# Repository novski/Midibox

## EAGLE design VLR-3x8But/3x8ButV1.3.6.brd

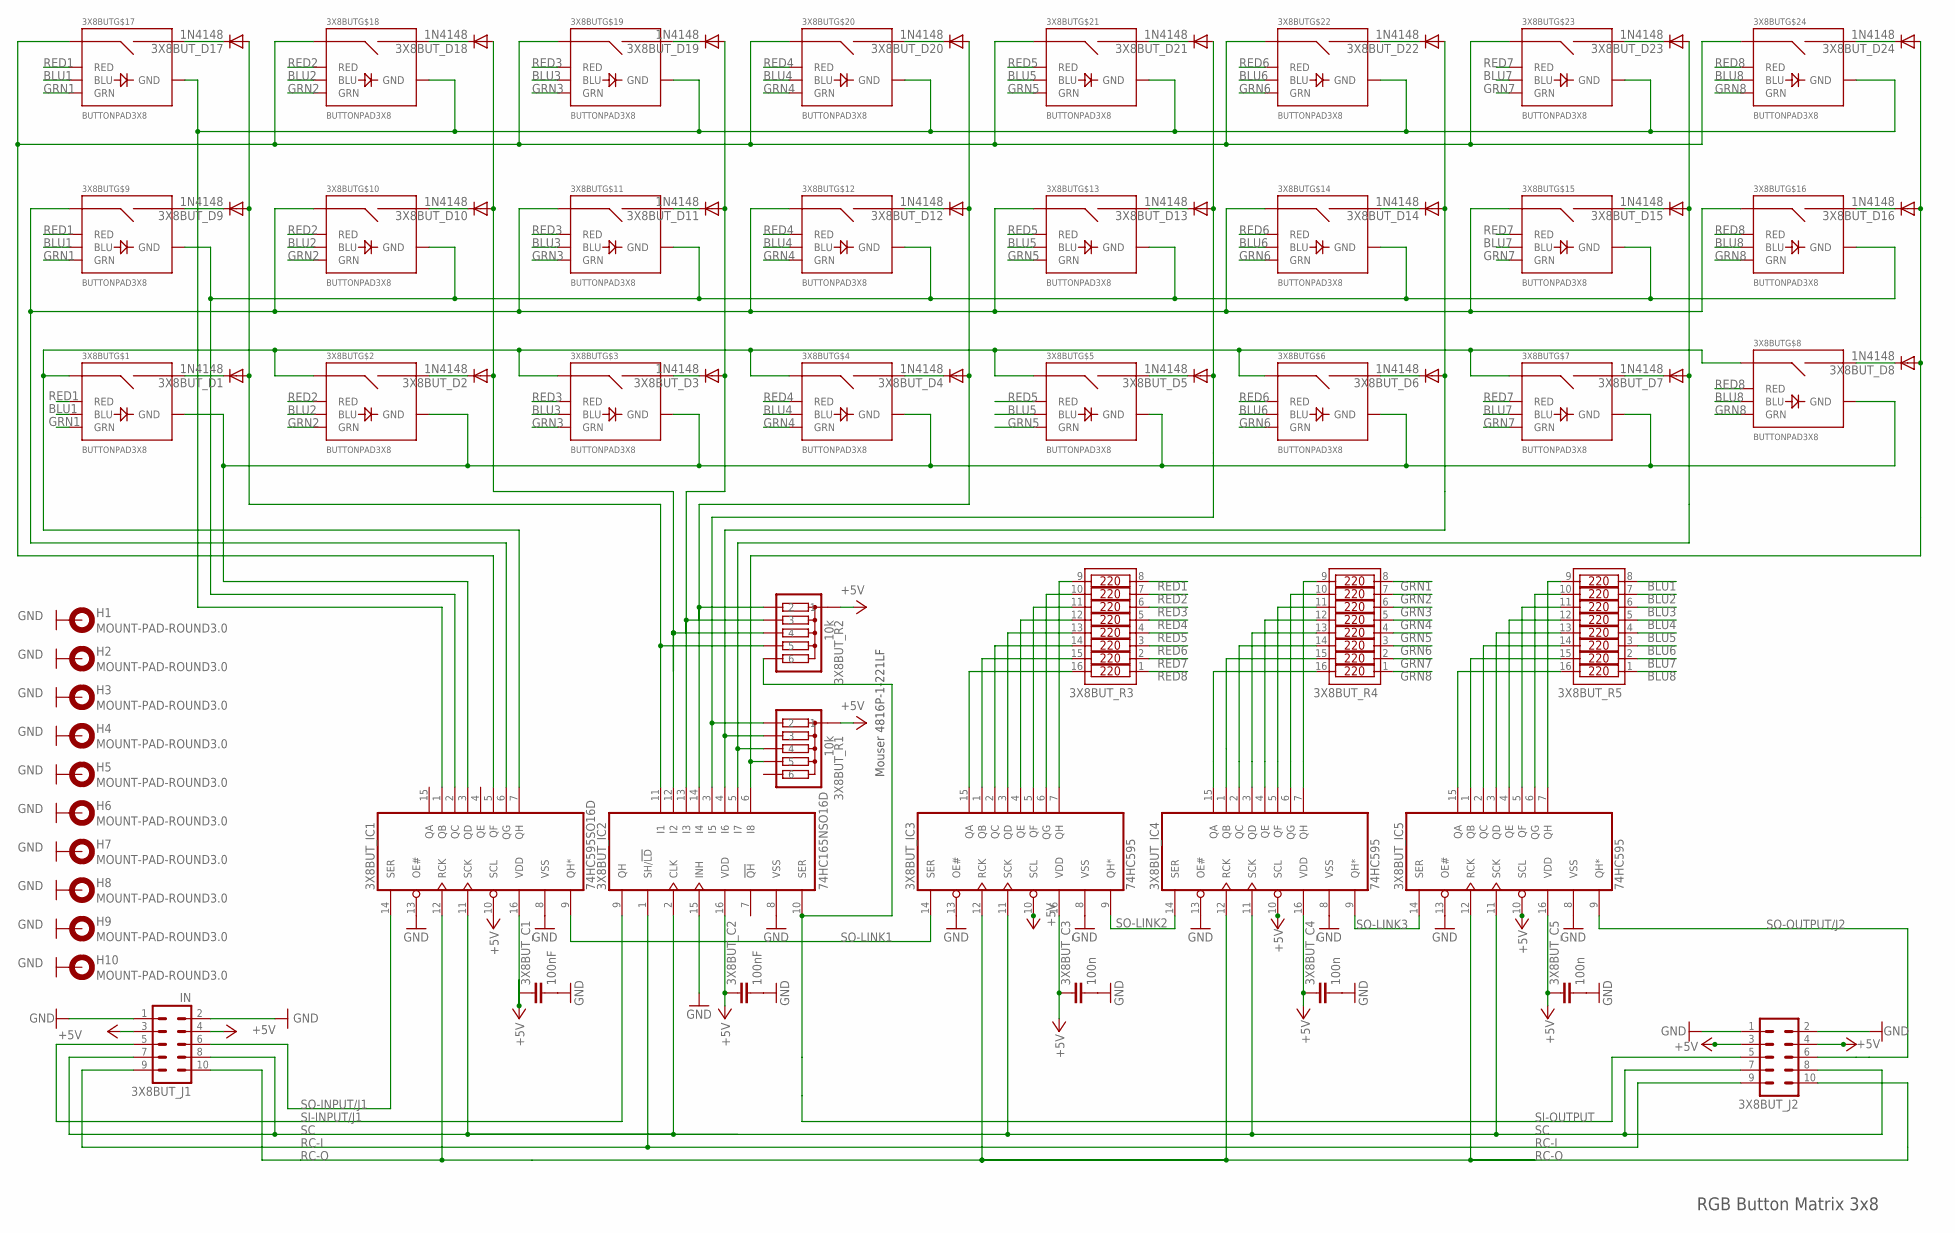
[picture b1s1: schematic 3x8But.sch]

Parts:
3X8BUT: BUTTONPAD3X8
3X8BUT_C1, 3X8BUT_C2: 100nF; C025-030X050
3X8BUT_C3, 3X8BUT_C4, 3X8BUT_C5: 100n; C025-030X050
3X8BUT_D1, 3X8BUT_D2, 3X8BUT_D3, 3X8BUT_D4, 3X8BUT_D5, 3X8BUT_D6, 3X8BUT_D7, 3X8BUT_D8, 3X8BUT_D9, 3X8BUT_D10, 3X8BUT_D11, 3X8BUT_D12, 3X8BUT_D13, 3X8BUT_D14, 3X8BUT_D15, 3X8BUT_D16, 3X8BUT_D17, 3X8BUT_D18, 3X8BUT_D19, 3X8BUT_D20, 3X8BUT_D21, 3X8BUT_D22, 3X8BUT_D23, 3X8BUT_D24: 1N4148; DO35-7
3X8BUT_IC1: 74HC595SO16D; SO16D
3X8BUT_IC2: 74HC165NSO16D; SO16D
3X8BUT_IC3, 3X8BUT_IC4, 3X8BUT_IC5: 74HC595; SO16D
3X8BUT_J1: IN; ML10
3X8BUT_J2: ML10
3X8BUT_R1, 3X8BUT_R2: 10k; SIL6
3X8BUT_R3, 3X8BUT_R4, 3X8BUT_R5: 4816P-1SOIC16W; SOIC16W
H1, H2, H3, H4, H5, H6, H7, H8, H9, H10: MOUNT-PAD-ROUND3.0; 3,0-PAD

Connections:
+5V: 3X8BUT_C1.1, 3X8BUT_C2.1, 3X8BUT_C3.1, 3X8BUT_C4.1, 3X8BUT_C5.1, 3X8BUT_IC1.10 (SCL), 3X8BUT_IC1.16 (VDD), 3X8BUT_IC2.16 (VDD), 3X8BUT_IC3.10 (SCL), 3X8BUT_IC3.16 (VDD), 3X8BUT_IC4.10 (SCL), 3X8BUT_IC4.16 (VDD), 3X8BUT_IC5.10 (SCL), 3X8BUT_IC5.16 (VDD), 3X8BUT_J1.3, 3X8BUT_J1.4, 3X8BUT_J2.3, 3X8BUT_J2.4, 3X8BUT_R1.1, 3X8BUT_R2.1
BLU1: 3X8BUT.BLU1 (BLU), 3X8BUT.BLU9 (BLU), 3X8BUT.BLU17 (BLU), 3X8BUT_R5.8
BLU2: 3X8BUT.BLU2 (BLU), 3X8BUT.BLU10 (BLU), 3X8BUT.BLU18 (BLU), 3X8BUT_R5.7
BLU3: 3X8BUT.BLU3 (BLU), 3X8BUT.BLU11 (BLU), 3X8BUT.BLU19 (BLU), 3X8BUT_R5.6
BLU4: 3X8BUT.BLU4 (BLU), 3X8BUT.BLU12 (BLU), 3X8BUT.BLU20 (BLU), 3X8BUT_R5.5
BLU5: 3X8BUT.BLU5 (BLU), 3X8BUT.BLU13 (BLU), 3X8BUT.BLU21 (BLU), 3X8BUT_R5.4
BLU6: 3X8BUT.BLU6 (BLU), 3X8BUT.BLU14 (BLU), 3X8BUT.BLU22 (BLU), 3X8BUT_R5.3
BLU7: 3X8BUT.BLU7 (BLU), 3X8BUT.BLU15 (BLU), 3X8BUT.BLU23 (BLU), 3X8BUT_R5.2
BLU8: 3X8BUT.BLU8 (BLU), 3X8BUT.BLU16 (BLU), 3X8BUT.BLU24 (BLU), 3X8BUT_R5.1
GND: 3X8BUT_C1.2, 3X8BUT_C2.2, 3X8BUT_C3.2, 3X8BUT_C4.2, 3X8BUT_C5.2, 3X8BUT_IC1.8 (VSS), 3X8BUT_IC1.13 (OE#), 3X8BUT_IC2.8 (VSS), 3X8BUT_IC2.15 (INH), 3X8BUT_IC3.8 (VSS), 3X8BUT_IC3.13 (OE#), 3X8BUT_IC4.8 (VSS), 3X8BUT_IC4.13 (OE#), 3X8BUT_IC5.8 (VSS), 3X8BUT_IC5.13 (OE#), 3X8BUT_J1.1, 3X8BUT_J1.2, 3X8BUT_J2.1, 3X8BUT_J2.2, H1.B3,0, H2.B3,0, H3.B3,0, H4.B3,0, H5.B3,0, H6.B3,0, H7.B3,0, H8.B3,0, H9.B3,0, H10.B3,0
GND1: 3X8BUT.GND1 (GND), 3X8BUT.GND2 (GND), 3X8BUT.GND3 (GND), 3X8BUT.GND4 (GND), 3X8BUT.GND5 (GND), 3X8BUT.GND6 (GND), 3X8BUT.GND7 (GND), 3X8BUT.GND8 (GND), 3X8BUT_IC1.3 (QD)
GND9: 3X8BUT.GND9 (GND), 3X8BUT.GND10 (GND), 3X8BUT.GND11 (GND), 3X8BUT.GND12 (GND), 3X8BUT.GND13 (GND), 3X8BUT.GND14 (GND), 3X8BUT.GND15 (GND), 3X8BUT.GND16 (GND), 3X8BUT_IC1.2 (QC)
GND17: 3X8BUT.GND17 (GND), 3X8BUT.GND18 (GND), 3X8BUT.GND19 (GND), 3X8BUT.GND20 (GND), 3X8BUT.GND21 (GND), 3X8BUT.GND22 (GND), 3X8BUT.GND23 (GND), 3X8BUT.GND24 (GND), 3X8BUT_IC1.1 (QB)
GRN1: 3X8BUT.GRN1 (GRN), 3X8BUT.GRN9 (GRN), 3X8BUT.GRN17 (GRN), 3X8BUT_R4.8
GRN2: 3X8BUT.GRN2 (GRN), 3X8BUT.GRN10 (GRN), 3X8BUT.GRN18 (GRN), 3X8BUT_R4.7
GRN3: 3X8BUT.GRN3 (GRN), 3X8BUT.GRN11 (GRN), 3X8BUT.GRN19 (GRN), 3X8BUT_R4.6
GRN4: 3X8BUT.GRN4 (GRN), 3X8BUT.GRN12 (GRN), 3X8BUT.GRN20 (GRN), 3X8BUT_R4.5
GRN5: 3X8BUT.GRN5 (GRN), 3X8BUT.GRN13 (GRN), 3X8BUT.GRN21 (GRN), 3X8BUT_R4.4
GRN6: 3X8BUT.GRN6 (GRN), 3X8BUT.GRN14 (GRN), 3X8BUT.GRN22 (GRN), 3X8BUT_R4.3
GRN7: 3X8BUT.GRN7 (GRN), 3X8BUT.GRN15 (GRN), 3X8BUT.GRN23 (GRN), 3X8BUT_R4.2
GRN8: 3X8BUT.GRN8 (GRN), 3X8BUT.GRN16 (GRN), 3X8BUT.GRN24 (GRN), 3X8BUT_R4.1
unnamed: 3X8BUT.SIG34 (SIG2), 3X8BUT_D17.C
unnamed: 3X8BUT.SIG18 (SIG2), 3X8BUT_D9.C
unnamed: 3X8BUT.SIG02 (SIG2), 3X8BUT_D1.C
unnamed: 3X8BUT.SIG36 (SIG2), 3X8BUT_D18.C
unnamed: 3X8BUT.SIG20 (SIG2), 3X8BUT_D10.C
unnamed: 3X8BUT.SIG04 (SIG2), 3X8BUT_D2.C
unnamed: 3X8BUT.SIG38 (SIG2), 3X8BUT_D19.C
unnamed: 3X8BUT.SIG22 (SIG2), 3X8BUT_D11.C
unnamed: 3X8BUT_IC5.15 (QA), 3X8BUT_R5.16
unnamed: 3X8BUT_IC5.1 (QB), 3X8BUT_R5.15
unnamed: 3X8BUT_IC5.2 (QC), 3X8BUT_R5.14
unnamed: 3X8BUT_IC5.3 (QD), 3X8BUT_R5.13
unnamed: 3X8BUT_IC5.4 (QE), 3X8BUT_R5.12
unnamed: 3X8BUT_IC5.5 (QF), 3X8BUT_R5.11
unnamed: 3X8BUT_IC5.6 (QG), 3X8BUT_R5.10
unnamed: 3X8BUT_IC5.7 (QH), 3X8BUT_R5.9
unnamed: 3X8BUT_IC3.15 (QA), 3X8BUT_R3.16
unnamed: 3X8BUT_IC3.1 (QB), 3X8BUT_R3.15
unnamed: 3X8BUT_IC3.2 (QC), 3X8BUT_R3.14
unnamed: 3X8BUT_IC3.3 (QD), 3X8BUT_R3.13
unnamed: 3X8BUT_IC3.4 (QE), 3X8BUT_R3.12
unnamed: 3X8BUT_IC3.5 (QF), 3X8BUT_R3.11
unnamed: 3X8BUT_IC3.6 (QG), 3X8BUT_R3.10
unnamed: 3X8BUT_IC3.7 (QH), 3X8BUT_R3.9
unnamed: 3X8BUT_IC4.15 (QA), 3X8BUT_R4.16
unnamed: 3X8BUT_IC4.1 (QB), 3X8BUT_R4.15
unnamed: 3X8BUT_IC4.2 (QC), 3X8BUT_R4.14
unnamed: 3X8BUT_IC4.3 (QD), 3X8BUT_R4.13
unnamed: 3X8BUT_IC4.4 (QE), 3X8BUT_R4.12
unnamed: 3X8BUT_IC4.5 (QF), 3X8BUT_R4.11
unnamed: 3X8BUT_IC4.6 (QG), 3X8BUT_R4.10
unnamed: 3X8BUT_IC4.7 (QH), 3X8BUT_R4.9
unnamed: 3X8BUT.SIG06 (SIG2), 3X8BUT_D3.C
unnamed: 3X8BUT.SIG40 (SIG2), 3X8BUT_D20.C
unnamed: 3X8BUT.SIG24 (SIG2), 3X8BUT_D12.C
unnamed: 3X8BUT.SIG08 (SIG2), 3X8BUT_D4.C
unnamed: 3X8BUT.SIG42 (SIG2), 3X8BUT_D21.C
unnamed: 3X8BUT.SIG26 (SIG2), 3X8BUT_D13.C
unnamed: 3X8BUT.SIG10 (SIG2), 3X8BUT_D5.C
unnamed: 3X8BUT.SIG44 (SIG2), 3X8BUT_D22.C
unnamed: 3X8BUT.SIG28 (SIG2), 3X8BUT_D14.C
unnamed: 3X8BUT.SIG12 (SIG2), 3X8BUT_D6.C
unnamed: 3X8BUT.SIG14 (SIG2), 3X8BUT_D7.C
unnamed: 3X8BUT.SIG30 (SIG2), 3X8BUT_D15.C
unnamed: 3X8BUT.SIG46 (SIG2), 3X8BUT_D23.C
unnamed: 3X8BUT.SIG48 (SIG2), 3X8BUT_D24.C
unnamed: 3X8BUT.SIG32 (SIG2), 3X8BUT_D16.C
unnamed: 3X8BUT.SIG16 (SIG2), 3X8BUT_D8.C
RC-I: 3X8BUT_IC2.1 (SH/!LD), 3X8BUT_J1.9, 3X8BUT_J2.9
RC-O: 3X8BUT_IC1.12 (RCK), 3X8BUT_IC3.12 (RCK), 3X8BUT_IC4.12 (RCK), 3X8BUT_IC5.12 (RCK), 3X8BUT_J1.10, 3X8BUT_J2.10
RED1: 3X8BUT.RED1 (RED), 3X8BUT.RED9 (RED), 3X8BUT.RED17 (RED), 3X8BUT_R3.8
RED2: 3X8BUT.RED2 (RED), 3X8BUT.RED10 (RED), 3X8BUT.RED18 (RED), 3X8BUT_R3.7
RED3: 3X8BUT.RED3 (RED), 3X8BUT.RED11 (RED), 3X8BUT.RED19 (RED), 3X8BUT_R3.6
RED4: 3X8BUT.RED4 (RED), 3X8BUT.RED12 (RED), 3X8BUT.RED20 (RED), 3X8BUT_R3.5
RED5: 3X8BUT.RED5 (RED), 3X8BUT.RED13 (RED), 3X8BUT.RED21 (RED), 3X8BUT_R3.4
RED6: 3X8BUT.RED6 (RED), 3X8BUT.RED14 (RED), 3X8BUT.RED22 (RED), 3X8BUT_R3.3
RED7: 3X8BUT.RED7 (RED), 3X8BUT.RED15 (RED), 3X8BUT.RED23 (RED), 3X8BUT_R3.2
RED8: 3X8BUT.RED8 (RED), 3X8BUT.RED16 (RED), 3X8BUT.RED24 (RED), 3X8BUT_R3.1
ROW1: 3X8BUT_D1.A, 3X8BUT_D9.A, 3X8BUT_D17.A, 3X8BUT_IC2.11 (I1), 3X8BUT_R2.5
ROW2: 3X8BUT_D2.A, 3X8BUT_D10.A, 3X8BUT_D18.A, 3X8BUT_IC2.12 (I2), 3X8BUT_R2.4
ROW3: 3X8BUT_D3.A, 3X8BUT_D11.A, 3X8BUT_D19.A, 3X8BUT_IC2.13 (I3), 3X8BUT_R2.3
ROW4: 3X8BUT_D4.A, 3X8BUT_D12.A, 3X8BUT_D20.A, 3X8BUT_IC2.14 (I4), 3X8BUT_R2.2
ROW5: 3X8BUT_D5.A, 3X8BUT_D13.A, 3X8BUT_D21.A, 3X8BUT_IC2.3 (I5), 3X8BUT_R1.2
ROW6: 3X8BUT_D6.A, 3X8BUT_D14.A, 3X8BUT_D22.A, 3X8BUT_IC2.4 (I6), 3X8BUT_R1.3
ROW7: 3X8BUT_D7.A, 3X8BUT_D15.A, 3X8BUT_D23.A, 3X8BUT_IC2.5 (I7), 3X8BUT_R1.4
ROW8: 3X8BUT_D8.A, 3X8BUT_D16.A, 3X8BUT_D24.A, 3X8BUT_IC2.6 (I8), 3X8BUT_R1.5
SC: 3X8BUT_IC1.11 (SCK), 3X8BUT_IC2.2 (CLK), 3X8BUT_IC3.11 (SCK), 3X8BUT_IC4.11 (SCK), 3X8BUT_IC5.11 (SCK), 3X8BUT_J1.7, 3X8BUT_J1.8, 3X8BUT_J2.7, 3X8BUT_J2.8
SEL1: 3X8BUT.SIG01 (SIG1), 3X8BUT.SIG03 (SIG1), 3X8BUT.SIG05 (SIG1), 3X8BUT.SIG07 (SIG1), 3X8BUT.SIG09 (SIG1), 3X8BUT.SIG11 (SIG1), 3X8BUT.SIG13 (SIG1), 3X8BUT.SIG15 (SIG1), 3X8BUT_IC1.7 (QH)
SEL2: 3X8BUT.SIG17 (SIG1), 3X8BUT.SIG19 (SIG1), 3X8BUT.SIG21 (SIG1), 3X8BUT.SIG23 (SIG1), 3X8BUT.SIG25 (SIG1), 3X8BUT.SIG27 (SIG1), 3X8BUT.SIG29 (SIG1), 3X8BUT.SIG31 (SIG1), 3X8BUT_IC1.6 (QG)
SEL3: 3X8BUT.SIG33 (SIG1), 3X8BUT.SIG35 (SIG1), 3X8BUT.SIG37 (SIG1), 3X8BUT.SIG39 (SIG1), 3X8BUT.SIG41 (SIG1), 3X8BUT.SIG43 (SIG1), 3X8BUT.SIG45 (SIG1), 3X8BUT.SIG47 (SIG1), 3X8BUT_IC1.5 (QF)
SI-INPUT/J1: 3X8BUT_IC2.9 (QH), 3X8BUT_J1.5
SI-OUTPUT: 3X8BUT_IC2.10 (SER), 3X8BUT_J2.5, 3X8BUT_R2.6
SO-INPUT/J1: 3X8BUT_IC1.14 (SER), 3X8BUT_J1.6
SO-LINK1: 3X8BUT_IC1.9 (QH*), 3X8BUT_IC3.14 (SER)
SO-LINK2: 3X8BUT_IC3.9 (QH*), 3X8BUT_IC4.14 (SER)
SO-LINK3: 3X8BUT_IC4.9 (QH*), 3X8BUT_IC5.14 (SER)
SO-OUTPUT/J2: 3X8BUT_IC5.9 (QH*), 3X8BUT_J2.6

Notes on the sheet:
RGB Button Matrix 3x8
Mouser 4816P-1-221LF

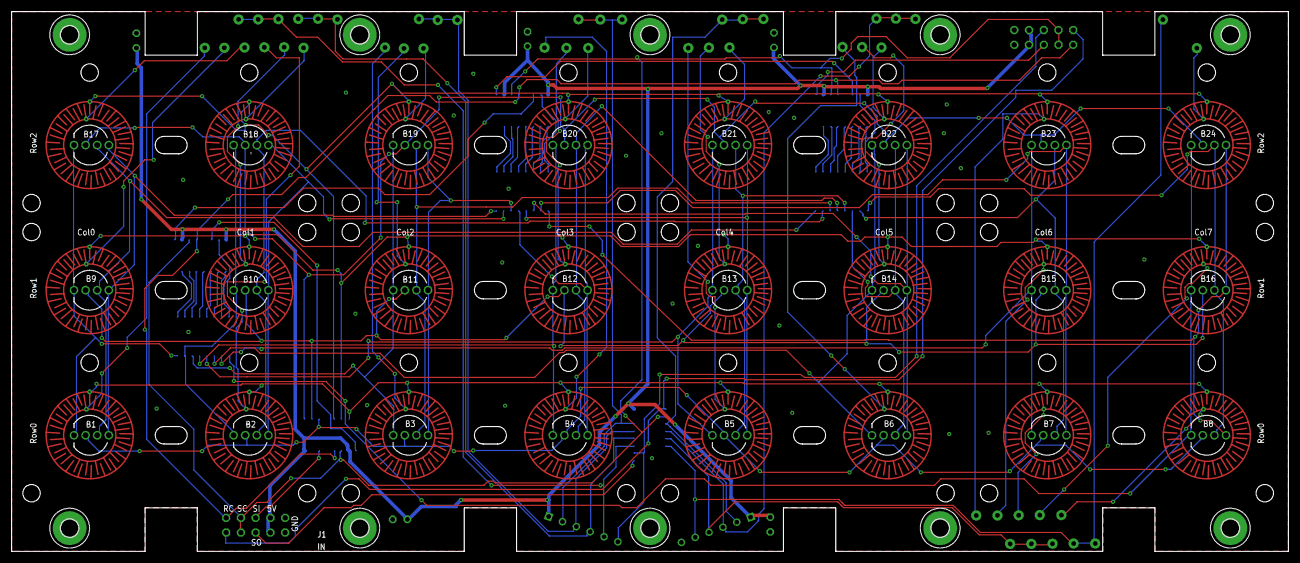
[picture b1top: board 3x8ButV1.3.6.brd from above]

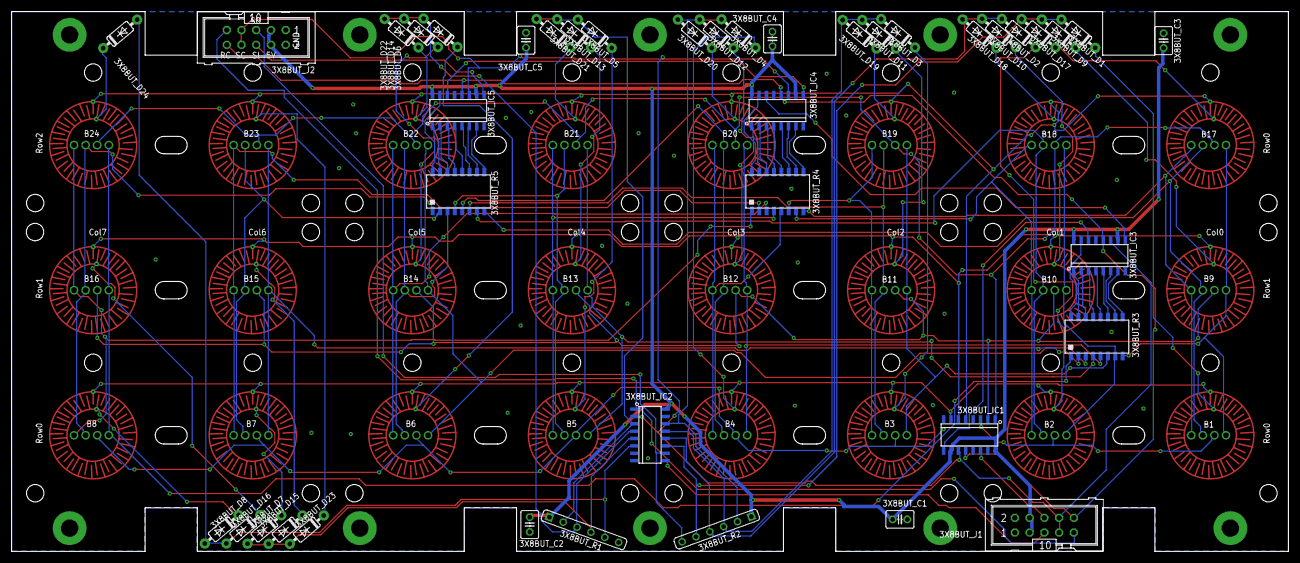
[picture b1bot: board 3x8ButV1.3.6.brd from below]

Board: 2 copper layers, 220.0 x 93.0 mm, 56 parts (43 on the bottom side), 98 nets.

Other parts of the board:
U$1, U$5: VLRLAB
U$3, U$4: 3X8BUT

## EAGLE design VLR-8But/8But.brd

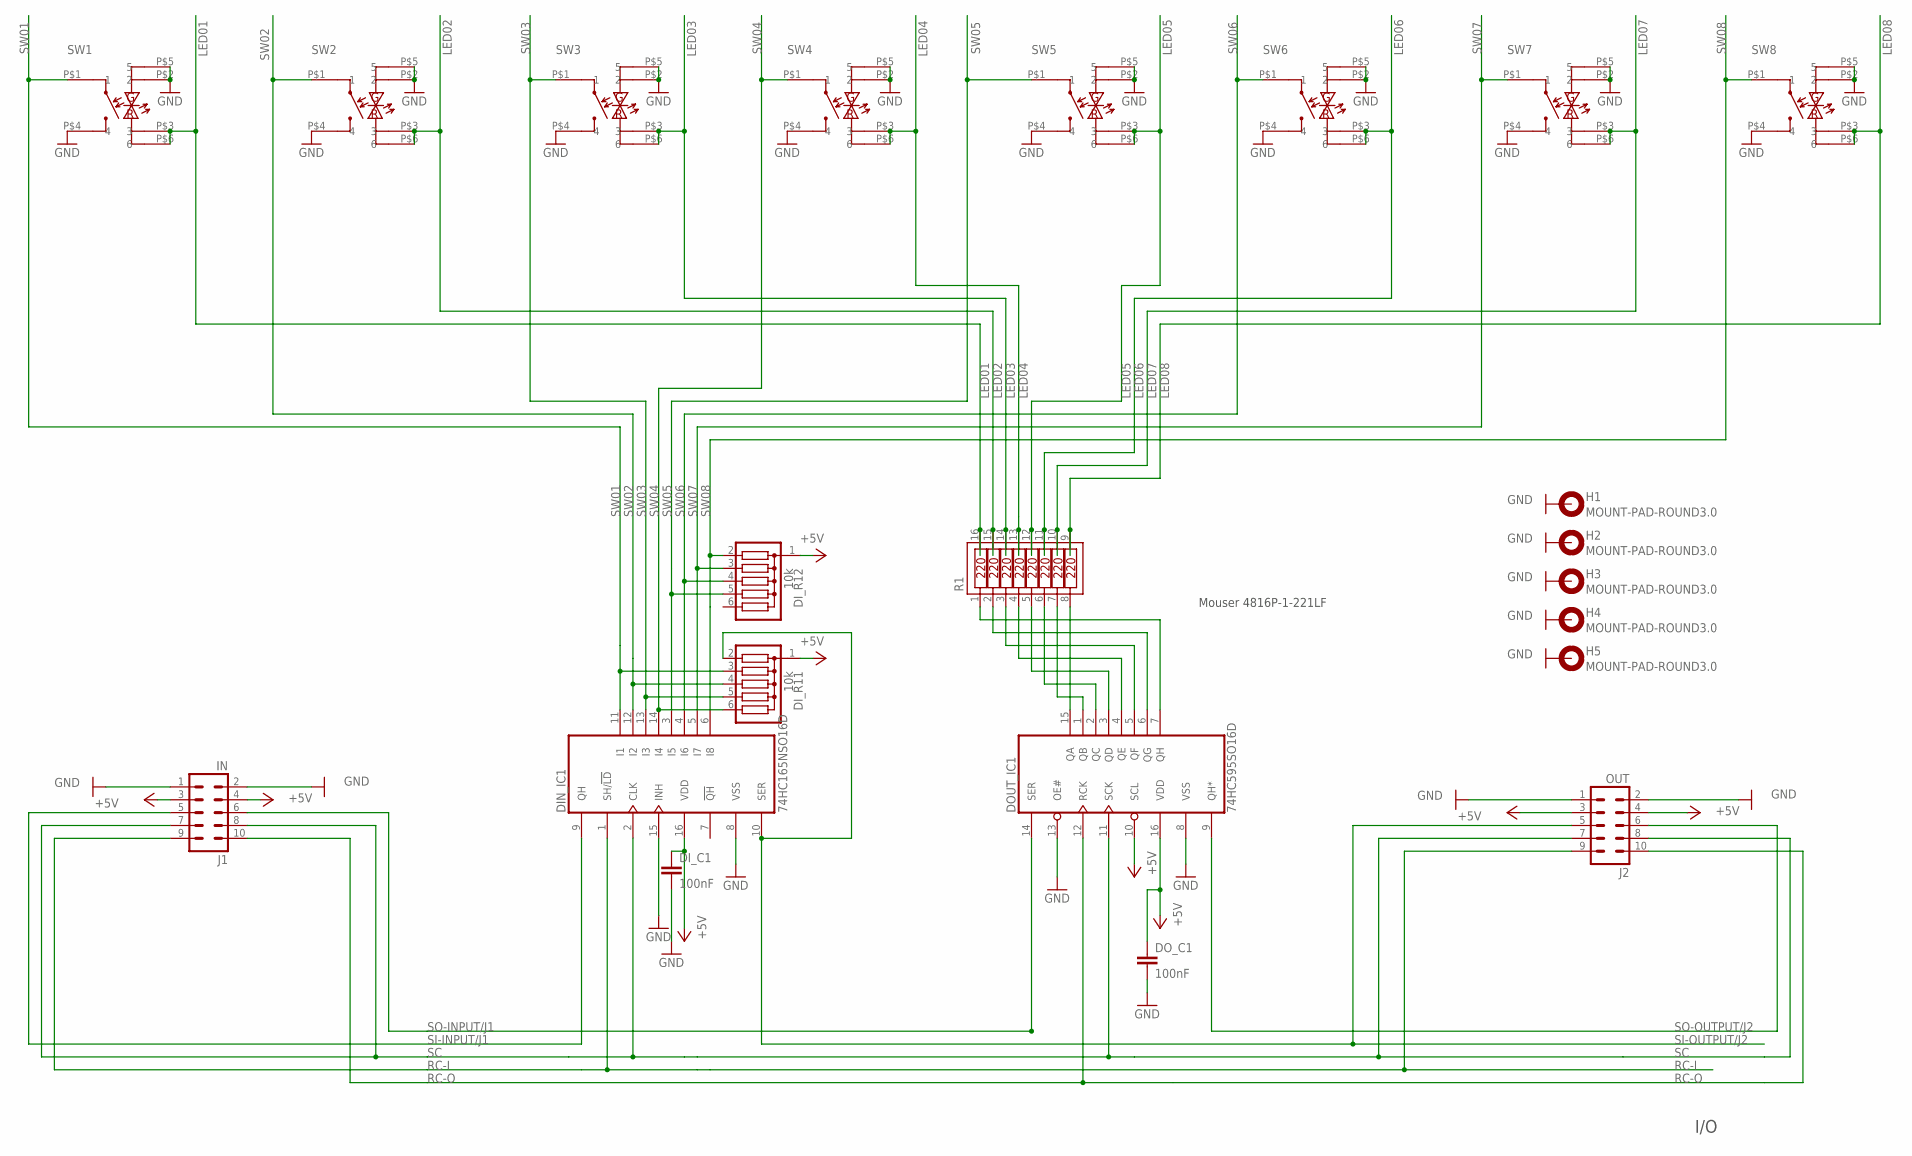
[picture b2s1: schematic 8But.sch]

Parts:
DIN_IC1: 74HC165NSO16D; SO16D
DI_C1: 100nF; C5B3
DI_R11, DI_R12: 10k; SIL6
DOUT_IC1: 74HC595SO16D; SO16D
DO_C1: 100nF; C5B3
H1, H2, H3, H4, H5: MOUNT-PAD-ROUND3.0; 3,0-PAD
J1: IN; ML10
J2: OUT; ML10
R1: 4816P-1SOIC16W; SOIC16W
SW1, SW2, SW3, SW4, SW5, SW6, SW7, SW8: COMB_G3+G5

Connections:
+5V: DIN_IC1.16 (VDD), DI_C1.1, DI_R11.1, DI_R12.1, DOUT_IC1.10 (SCL), DOUT_IC1.16 (VDD), DO_C1.1, J1.3, J1.4, J2.3, J2.4
GND: DIN_IC1.8 (VSS), DIN_IC1.15 (INH), DI_C1.2, DOUT_IC1.8 (VSS), DOUT_IC1.13 (OE#), DO_C1.2, H1.B3,0, H2.B3,0, H3.B3,0, H4.B3,0, H5.B3,0, J1.1, J1.2, J2.1, J2.2, SW1.P$2 (2), SW1.P$4 (4), SW1.P$5 (5), SW2.P$2 (2), SW2.P$4 (4), SW2.P$5 (5), SW3.P$2 (2), SW3.P$4 (4), SW3.P$5 (5), SW4.P$2 (2), SW4.P$4 (4), SW4.P$5 (5), SW5.P$2 (2), SW5.P$4 (4), SW5.P$5 (5), SW6.P$2 (2), SW6.P$4 (4), SW6.P$5 (5), SW7.P$2 (2), SW7.P$4 (4), SW7.P$5 (5), SW8.P$2 (2), SW8.P$4 (4), SW8.P$5 (5)
LED01: R1.16, SW1.P$3 (3), SW1.P$6 (6)
LED02: R1.15, SW2.P$3 (3), SW2.P$6 (6)
LED03: R1.14, SW3.P$3 (3), SW3.P$6 (6)
LED04: R1.13, SW4.P$3 (3), SW4.P$6 (6)
LED05: R1.12, SW5.P$3 (3), SW5.P$6 (6)
LED06: R1.11, SW6.P$3 (3), SW6.P$6 (6)
LED07: R1.10, SW7.P$3 (3), SW7.P$6 (6)
LED08: R1.9, SW8.P$3 (3), SW8.P$6 (6)
unnamed: DOUT_IC1.15 (QA), R1.8
unnamed: DOUT_IC1.1 (QB), R1.7
unnamed: DOUT_IC1.2 (QC), R1.6
unnamed: DOUT_IC1.3 (QD), R1.5
unnamed: DOUT_IC1.4 (QE), R1.4
unnamed: DOUT_IC1.5 (QF), R1.3
unnamed: DOUT_IC1.6 (QG), R1.2
unnamed: DOUT_IC1.7 (QH), R1.1
RC-I: DIN_IC1.1 (SH/!LD), J1.9, J2.9
RC-O: DOUT_IC1.12 (RCK), J1.10, J2.10
SC: DIN_IC1.2 (CLK), DOUT_IC1.11 (SCK), J1.7, J1.8, J2.7, J2.8
SI-INPUT/J1: DIN_IC1.9 (QH), J1.5
SI-OUTPUT/J2: DIN_IC1.10 (SER), DI_R11.2, J2.5
SO-INPUT/J1: DOUT_IC1.14 (SER), J1.6
SO-OUTPUT/J2: DOUT_IC1.9 (QH*), J2.6
SW01: DIN_IC1.11 (I1), DI_R11.3, SW1.P$1 (1)
SW02: DIN_IC1.12 (I2), DI_R11.4, SW2.P$1 (1)
SW03: DIN_IC1.13 (I3), DI_R11.5, SW3.P$1 (1)
SW04: DIN_IC1.14 (I4), DI_R11.6, SW4.P$1 (1)
SW05: DIN_IC1.3 (I5), DI_R12.5, SW5.P$1 (1)
SW06: DIN_IC1.4 (I6), DI_R12.4, SW6.P$1 (1)
SW07: DIN_IC1.5 (I7), DI_R12.3, SW7.P$1 (1)
SW08: DIN_IC1.6 (I8), DI_R12.2, SW8.P$1 (1)

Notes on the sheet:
I/O
Mouser 4816P-1-221LF

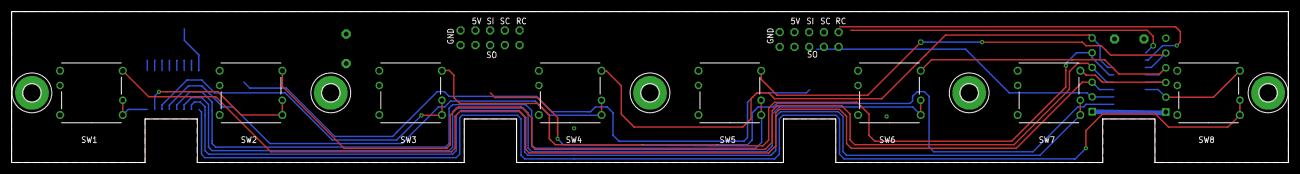
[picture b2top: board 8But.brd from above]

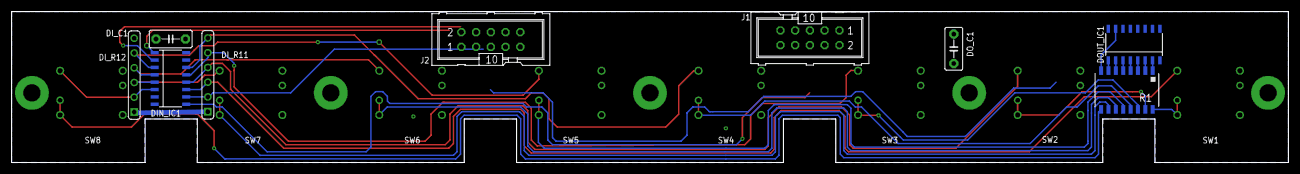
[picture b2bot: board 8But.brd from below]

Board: 2 copper layers, 220.0 x 26.0 mm, 26 parts (11 on the bottom side), 33 nets.

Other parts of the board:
U$1, U$5: VLRLAB
U$3, U$4: 8BUT

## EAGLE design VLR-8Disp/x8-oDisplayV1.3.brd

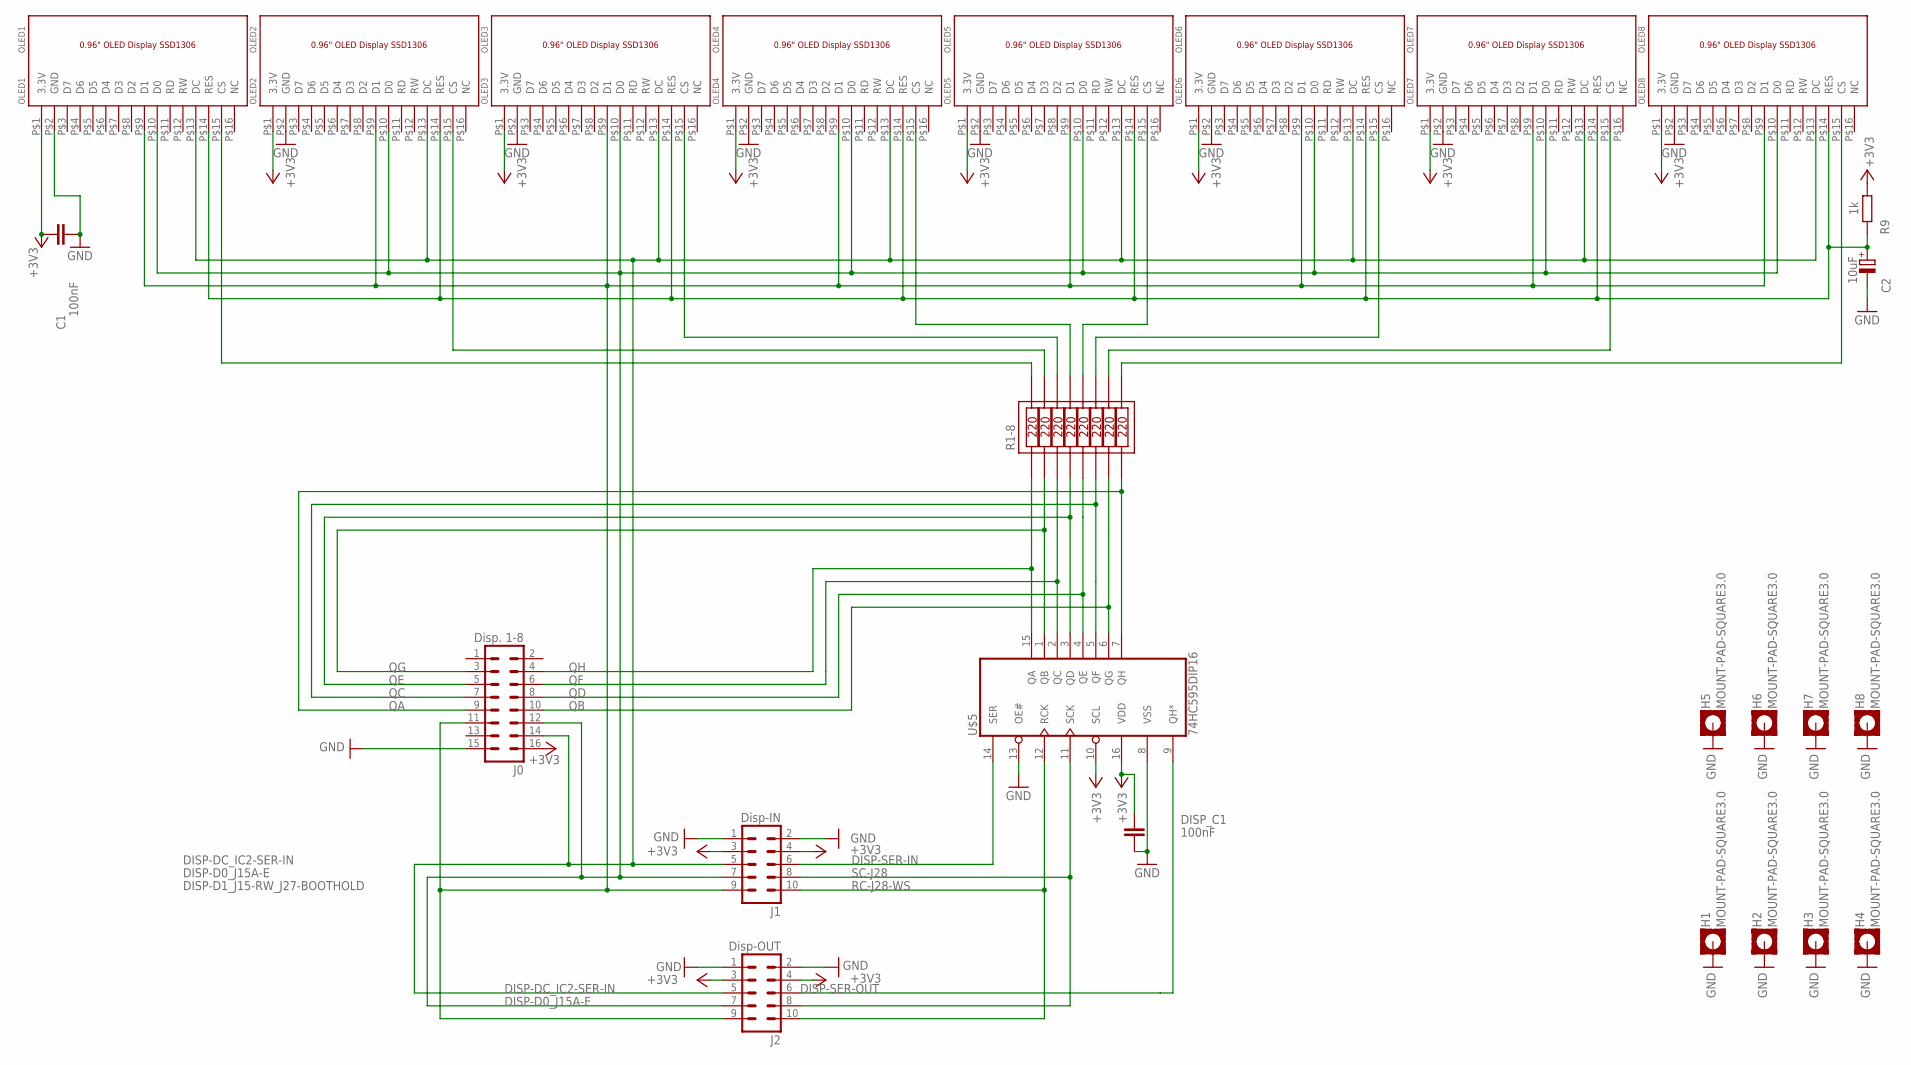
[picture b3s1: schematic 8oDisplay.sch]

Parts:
C1: 100nF; C5B3
C2: 10uF; E2,5-6
DISP_C1: 100nF; C5B3
H1, H2, H3, H4, H5, H6, H7, H8: MOUNT-PAD-SQUARE3.0; 3,0-PAD-SQUARE
J0: Disp. 1-8; ML16
J1: Disp-IN; ML10
J2: Disp-OUT; ML10
OLED1: OLED1; 0.96"
OLED2: OLED2; 0.96"
OLED3: OLED3; 0.96"
OLED4: OLED4; 0.96"
OLED5: OLED5; 0.96"
OLED6: OLED6; 0.96"
OLED7: OLED7; 0.96"
OLED8: OLED8; 0.96"
R1-8: 4116R; DIL16
R9: 1k; 0204/7
U$5: 74HC595DIP16; DIL16

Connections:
+3V3: C1.1, DISP_C1.1, J0.16, J1.3, J1.4, J2.3, J2.4, OLED1.P$1 (3.3V), OLED2.P$1 (3.3V), OLED3.P$1 (3.3V), OLED4.P$1 (3.3V), OLED5.P$1 (3.3V), OLED6.P$1 (3.3V), OLED7.P$1 (3.3V), OLED8.P$1 (3.3V), R9.2, U$5.10 (SCL), U$5.16 (VDD)
DISP-D0_J15A-E: J0.12, J1.7, J2.7, OLED1.P$10 (D0), OLED2.P$10 (D0), OLED3.P$10 (D0), OLED4.P$10 (D0), OLED5.P$10 (D0), OLED6.P$10 (D0), OLED7.P$10 (D0), OLED8.P$10 (D0)
DISP-D1_J15-RW_J27-BOOTHOLD: J0.11, J1.9, J2.9, OLED1.P$9 (D1), OLED2.P$9 (D1), OLED3.P$9 (D1), OLED4.P$9 (D1), OLED5.P$9 (D1), OLED6.P$9 (D1), OLED7.P$9 (D1), OLED8.P$9 (D1)
DISP-DC_IC2-SER-IN: J0.14, J1.5, J2.5, OLED1.P$13 (DC), OLED2.P$13 (DC), OLED3.P$13 (DC), OLED4.P$13 (DC), OLED5.P$13 (DC), OLED6.P$13 (DC), OLED7.P$13 (DC), OLED8.P$13 (DC)
DISP-SER-IN: J1.6, U$5.14 (SER)
DISP-SER-OUT: J2.6, U$5.9 (QH*)
GND: C1.2, C2.-, DISP_C1.2, H1.B3,0, H2.B3,0, H3.B3,0, H4.B3,0, H5.B3,0, H6.B3,0, H7.B3,0, H8.B3,0, J0.15, J1.1, J1.2, J2.1, J2.2, OLED1.P$2 (GND), OLED2.P$2 (GND), OLED3.P$2 (GND), OLED4.P$2 (GND), OLED5.P$2 (GND), OLED6.P$2 (GND), OLED7.P$2 (GND), OLED8.P$2 (GND), U$5.8 (VSS), U$5.13 (OE#)
QA: J0.9, R1-8.16, U$5.7 (QH)
QAA: OLED8.P$15 (CS), R1-8.8
QB: J0.10, R1-8.15, U$5.6 (QG)
QBB: OLED7.P$15 (CS), R1-8.7
QC: J0.7, R1-8.14, U$5.5 (QF)
QCC: OLED6.P$15 (CS), R1-8.6
QD: J0.8, R1-8.13, U$5.4 (QE)
QDD: OLED5.P$15 (CS), R1-8.5
QE: J0.5, R1-8.12, U$5.3 (QD)
QEE: OLED4.P$15 (CS), R1-8.4
QF: J0.6, R1-8.11, U$5.2 (QC)
QFF: OLED3.P$15 (CS), R1-8.3
QG: J0.3, R1-8.10, U$5.1 (QB)
QGG: OLED2.P$15 (CS), R1-8.2
QH: J0.4, R1-8.9, U$5.15 (QA)
QHH: OLED1.P$15 (CS), R1-8.1
RC-J28-WS: J1.10, J2.10, U$5.12 (RCK)
RST: C2.+, OLED1.P$14 (RES), OLED2.P$14 (RES), OLED3.P$14 (RES), OLED4.P$14 (RES), OLED5.P$14 (RES), OLED6.P$14 (RES), OLED7.P$14 (RES), OLED8.P$14 (RES), R9.1
SC-J28: J1.8, J2.8, U$5.11 (SCK)

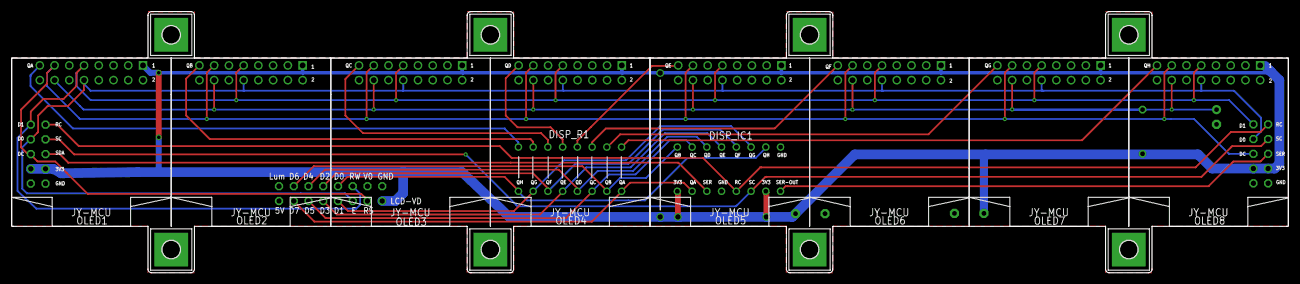
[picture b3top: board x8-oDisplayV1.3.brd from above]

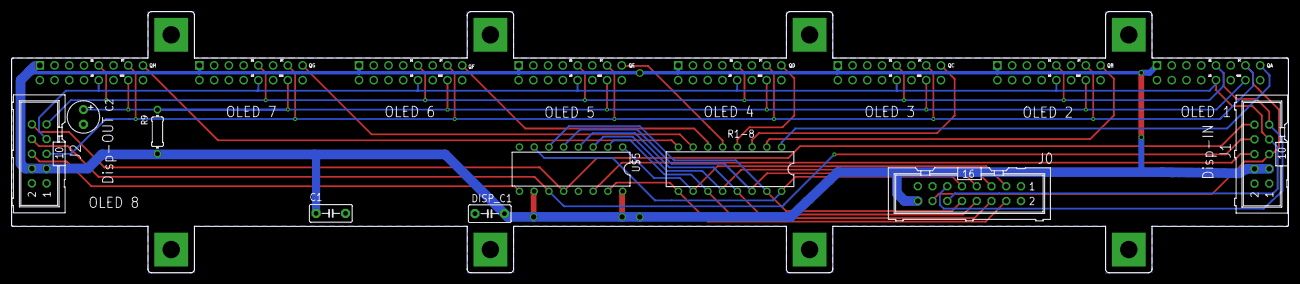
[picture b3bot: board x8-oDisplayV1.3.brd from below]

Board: 2 copper layers, 220.0 x 45.0 mm, 28 parts (12 on the bottom side), 26 nets.

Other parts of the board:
U$1: X8ODISPLAY
U$2: VLRLAB
U$4: (C)T.KLOSE

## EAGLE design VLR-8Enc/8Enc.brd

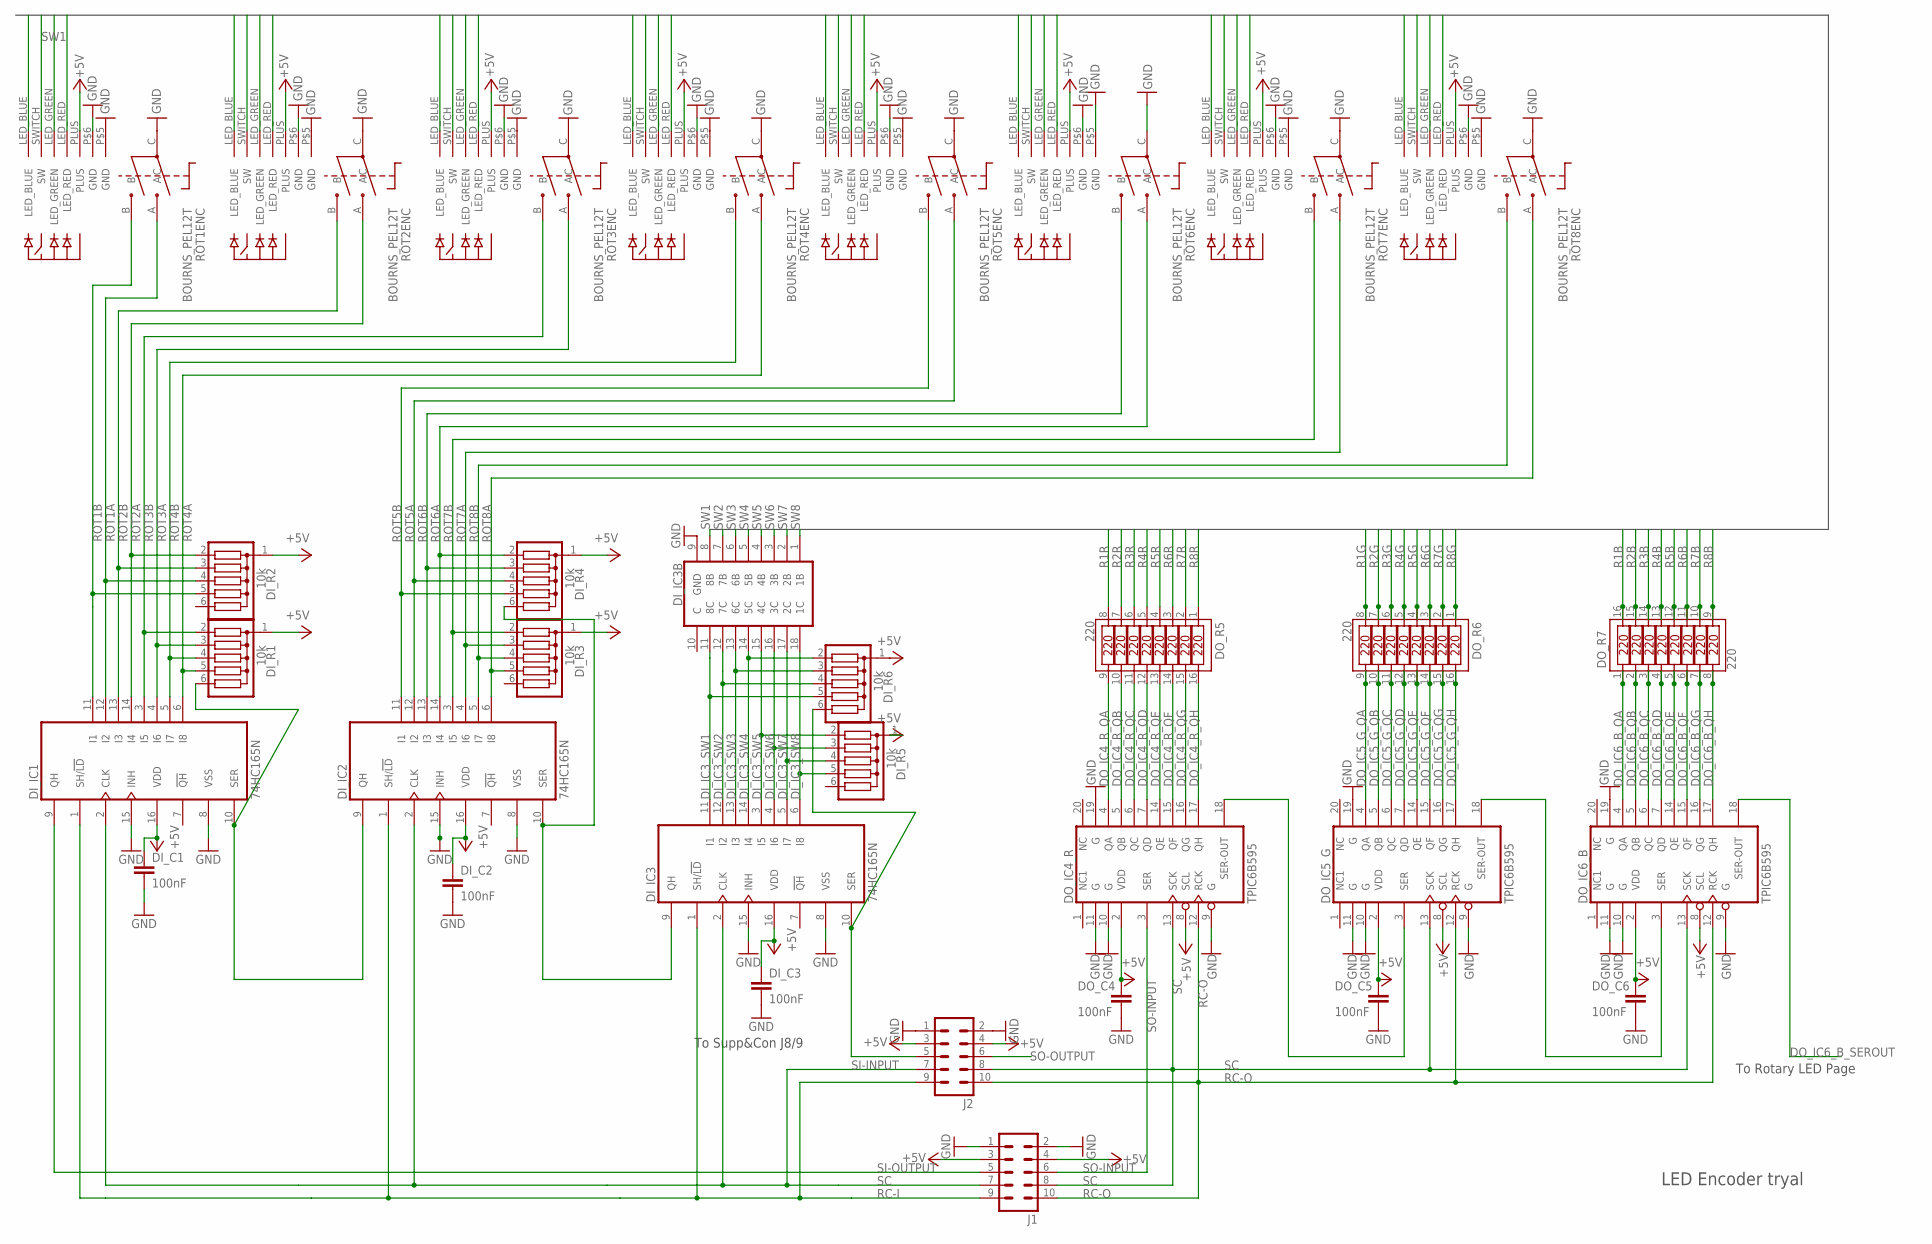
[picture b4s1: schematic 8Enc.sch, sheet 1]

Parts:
DI_C1, DI_C2, DI_C3: 100nF; C025-024X044
DI_IC1, DI_IC2, DI_IC3: 74HC165N; SO16D
DI_IC3B: ULN2803SO18W; SO18W
DI_R1, DI_R2, DI_R3, DI_R4, DI_R5, DI_R6: 10k; SIL6
DO_C4, DO_C5, DO_C6: 100nF; C025-024X044
DO_IC4_R, DO_IC5_G, DO_IC6_B: TPIC6B595; SO20W
DO_R5, DO_R6, DO_R7: 220; SOIC16W
J1, J2: ML10
ROT1, ROT2, ROT3, ROT4, ROT5, ROT6, ROT7, ROT8: BOURNS_PEL12T; PEL12T_11-LED-RING

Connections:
+5V: DI_C1.1, DI_C2.1, DI_C3.1, DI_IC1.16 (VDD), DI_IC2.16 (VDD), DI_IC3.16 (VDD), DI_R1.1, DI_R2.1, DI_R3.1, DI_R4.1, DI_R5.1, DI_R6.1, DO_C4.1, DO_C5.1, DO_C6.1, DO_IC4_R.2 (VDD), DO_IC4_R.8 (SCL), DO_IC5_G.2 (VDD), DO_IC5_G.8 (SCL), DO_IC6_B.2 (VDD), DO_IC6_B.8 (SCL), J1.3, J1.4, J2.3, J2.4, ROT1.PLUS, ROT2.PLUS, ROT3.PLUS, ROT4.PLUS, ROT5.PLUS, ROT6.PLUS, ROT7.PLUS, ROT8.PLUS; also elsewhere on the board
DI_IC3_SW1: DI_IC3.11 (I1), DI_IC3B.11 (8C), DI_R6.5
DI_IC3_SW2: DI_IC3.12 (I2), DI_IC3B.12 (7C), DI_R6.4
DI_IC3_SW3: DI_IC3.13 (I3), DI_IC3B.13 (6C), DI_R6.3
DI_IC3_SW4: DI_IC3.14 (I4), DI_IC3B.14 (5C), DI_R6.2
DI_IC3_SW5: DI_IC3.3 (I5), DI_IC3B.15 (4C), DI_R5.2
DI_IC3_SW6: DI_IC3.4 (I6), DI_IC3B.16 (3C), DI_R5.3
DI_IC3_SW7: DI_IC3.5 (I7), DI_IC3B.17 (2C), DI_R5.4
DI_IC3_SW8: DI_IC3.6 (I8), DI_IC3B.18 (1C), DI_R5.5
DI_IC4_SER_OUT2: DI_IC1.10 (SER), DI_IC2.9 (QH), DI_R1.6
DI_IC5_SER_OUT2: DI_IC2.10 (SER), DI_IC3.9 (QH), DI_R4.6
DO_IC4_R_QA: DO_IC4_R.4 (QA), DO_R5.9
DO_IC4_R_QB: DO_IC4_R.5 (QB), DO_R5.10
DO_IC4_R_QC: DO_IC4_R.6 (QC), DO_R5.11
DO_IC4_R_QD: DO_IC4_R.7 (QD), DO_R5.12
DO_IC4_R_QE: DO_IC4_R.14 (QE), DO_R5.13
DO_IC4_R_QF: DO_IC4_R.15 (QF), DO_R5.14
DO_IC4_R_QG: DO_IC4_R.16 (QG), DO_R5.15
DO_IC4_R_QH: DO_IC4_R.17 (QH), DO_R5.16
DO_IC4_R_SEROUT: DO_IC4_R.18 (SER-OUT), DO_IC5_G.3 (SER)
DO_IC5_G_QA: DO_IC5_G.4 (QA), DO_R6.9
DO_IC5_G_QB: DO_IC5_G.5 (QB), DO_R6.10
DO_IC5_G_QC: DO_IC5_G.6 (QC), DO_R6.11
DO_IC5_G_QD: DO_IC5_G.7 (QD), DO_R6.12
DO_IC5_G_QE: DO_IC5_G.14 (QE), DO_R6.13
DO_IC5_G_QF: DO_IC5_G.15 (QF), DO_R6.14
DO_IC5_G_QG: DO_IC5_G.16 (QG), DO_R6.15
DO_IC5_G_QH: DO_IC5_G.17 (QH), DO_R6.16
DO_IC5_G_SEROUT: DO_IC5_G.18 (SER-OUT), DO_IC6_B.3 (SER)
DO_IC6_B_QA: DO_IC6_B.4 (QA), DO_R7.1
DO_IC6_B_QB: DO_IC6_B.5 (QB), DO_R7.2
DO_IC6_B_QC: DO_IC6_B.6 (QC), DO_R7.3
DO_IC6_B_QD: DO_IC6_B.7 (QD), DO_R7.4
DO_IC6_B_QE: DO_IC6_B.14 (QE), DO_R7.5
DO_IC6_B_QF: DO_IC6_B.15 (QF), DO_R7.6
DO_IC6_B_QG: DO_IC6_B.16 (QG), DO_R7.7
DO_IC6_B_QH: DO_IC6_B.17 (QH), DO_R7.8
DO_IC6_B_SEROUT: DO_IC6_B.18 (SER-OUT); also elsewhere on the board
GND: DI_C1.2, DI_C2.2, DI_C3.2, DI_IC1.8 (VSS), DI_IC1.15 (INH), DI_IC2.8 (VSS), DI_IC2.15 (INH), DI_IC3.8 (VSS), DI_IC3.15 (INH), DI_IC3B.9 (GND), DO_C4.2, DO_C5.2, DO_C6.2, DO_IC4_R.9 (G), DO_IC4_R.10 (G), DO_IC4_R.11 (G), DO_IC4_R.19 (G), DO_IC5_G.9 (G), DO_IC5_G.10 (G), DO_IC5_G.11 (G), DO_IC5_G.19 (G), DO_IC6_B.9 (G), DO_IC6_B.10 (G), DO_IC6_B.11 (G), DO_IC6_B.19 (G), J1.1, J1.2, J2.1, J2.2, ROT1.C, ROT1.P$5 (GND), ROT1.P$6 (GND), ROT2.C, ROT2.P$5 (GND), ROT2.P$6 (GND), ROT3.C, ROT3.P$5 (GND), ROT3.P$6 (GND), ROT4.C, ROT4.P$5 (GND), ROT4.P$6 (GND), ROT5.C, ROT5.P$5 (GND), ROT5.P$6 (GND), ROT6.C, ROT6.P$5 (GND), ROT6.P$6 (GND), ROT7.C, ROT7.P$5 (GND), ROT7.P$6 (GND), ROT8.C, ROT8.P$5 (GND), ROT8.P$6 (GND); also elsewhere on the board
R1B: DO_R7.16, ROT1.LED_BLUE
R1G: DO_R6.8, ROT1.LED_GREEN
R1R: DO_R5.8, ROT1.LED_RED
R2B: DO_R7.15, ROT2.LED_BLUE
R2G: DO_R6.7, ROT2.LED_GREEN
R2R: DO_R5.7, ROT2.LED_RED
R3B: DO_R7.14, ROT3.LED_BLUE
R3G: DO_R6.6, ROT3.LED_GREEN
R3R: DO_R5.6, ROT3.LED_RED
R4B: DO_R7.13, ROT4.LED_BLUE
R4G: DO_R6.5, ROT4.LED_GREEN
R4R: DO_R5.5, ROT4.LED_RED
R5B: DO_R7.12, ROT5.LED_BLUE
R5G: DO_R6.4, ROT5.LED_GREEN
R5R: DO_R5.4, ROT5.LED_RED
R6B: DO_R7.11, ROT6.LED_BLUE
R6G: DO_R6.3, ROT6.LED_GREEN
R6R: DO_R5.3, ROT6.LED_RED
R7B: DO_R7.10, ROT7.LED_BLUE
R7G: DO_R6.2, ROT7.LED_GREEN
R7R: DO_R5.2, ROT7.LED_RED
R8B: DO_R7.9, ROT8.LED_BLUE
R8G: DO_R6.1, ROT8.LED_GREEN
R8R: DO_R5.1, ROT8.LED_RED
RC-I: DI_IC1.1 (SH/!LD), DI_IC2.1 (SH/!LD), DI_IC3.1 (SH/!LD), J1.9, J2.9
RC-O: DO_IC4_R.12 (RCK), DO_IC5_G.12 (RCK), DO_IC6_B.12 (RCK), J1.10, J2.10; also elsewhere on the board
ROT1A: DI_IC1.12 (I2), DI_R2.4, ROT1.A
ROT1B: DI_IC1.11 (I1), DI_R2.5, ROT1.B
ROT2A: DI_IC1.14 (I4), DI_R2.2, ROT2.A
ROT2B: DI_IC1.13 (I3), DI_R2.3, ROT2.B
ROT3A: DI_IC1.4 (I6), DI_R1.3, ROT3.A
ROT3B: DI_IC1.3 (I5), DI_R1.2, ROT3.B
ROT4A: DI_IC1.6 (I8), DI_R1.5, ROT4.A
ROT4B: DI_IC1.5 (I7), DI_R1.4, ROT4.B
ROT5A: DI_IC2.12 (I2), DI_R4.4, ROT5.A
ROT5B: DI_IC2.11 (I1), DI_R4.5, ROT5.B
ROT6A: DI_IC2.14 (I4), DI_R4.2, ROT6.A
ROT6B: DI_IC2.13 (I3), DI_R4.3, ROT6.B
ROT7A: DI_IC2.4 (I6), DI_R3.3, ROT7.A
ROT7B: DI_IC2.3 (I5), DI_R3.2, ROT7.B
ROT8A: DI_IC2.6 (I8), DI_R3.5, ROT8.A
ROT8B: DI_IC2.5 (I7), DI_R3.4, ROT8.B
SC: DI_IC1.2 (CLK), DI_IC2.2 (CLK), DI_IC3.2 (CLK), DO_IC4_R.13 (SCK), DO_IC5_G.13 (SCK), DO_IC6_B.13 (SCK), J1.7, J1.8, J2.7, J2.8; also elsewhere on the board
SI-INPUT: DI_IC3.10 (SER), DI_R6.6, J2.5
SI-OUTPUT: DI_IC1.9 (QH), J1.5
SO-INPUT: DO_IC4_R.3 (SER), J1.6
SO-OUTPUT: J2.6; also elsewhere on the board
SW1: DI_IC3B.8 (8B), ROT1.SWITCH (SW)
SW2: DI_IC3B.7 (7B), ROT2.SWITCH (SW)
SW3: DI_IC3B.6 (6B), ROT3.SWITCH (SW)
SW4: DI_IC3B.5 (5B), ROT4.SWITCH (SW)
SW5: DI_IC3B.4 (4B), ROT5.SWITCH (SW)
SW6: DI_IC3B.3 (3B), ROT6.SWITCH (SW)
SW7: DI_IC3B.2 (2B), ROT7.SWITCH (SW)
SW8: DI_IC3B.1 (1B), ROT8.SWITCH (SW)

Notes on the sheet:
LED Encoder tryal
To Supp&Con J8/9
To Rotary LED Page
